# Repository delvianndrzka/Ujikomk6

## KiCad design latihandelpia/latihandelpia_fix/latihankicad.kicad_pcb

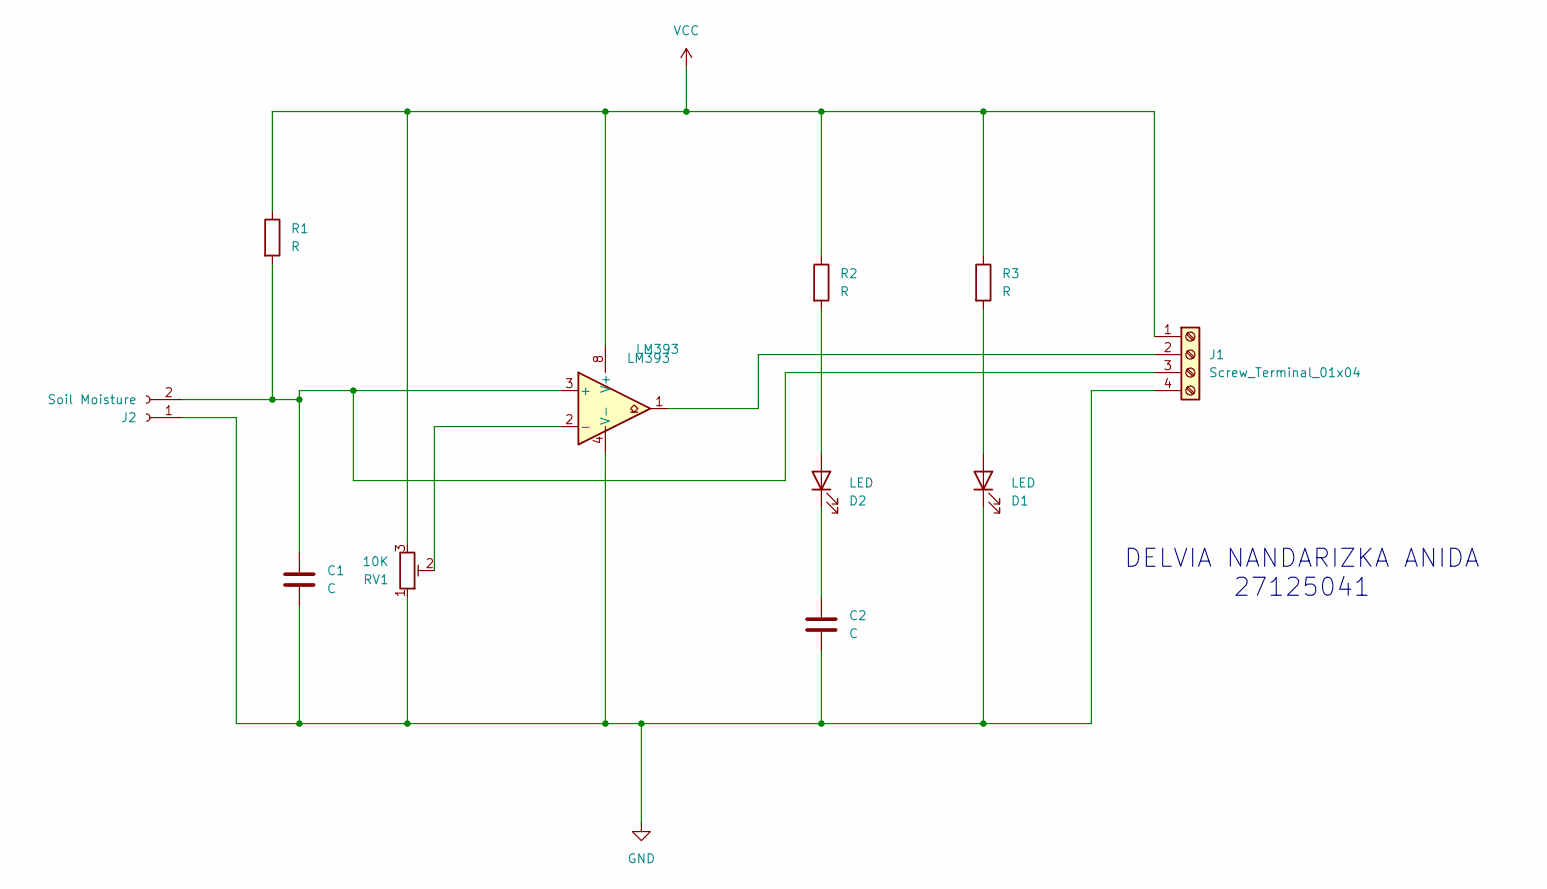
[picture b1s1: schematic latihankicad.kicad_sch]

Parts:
C1, C2: C; C_Axial_L22.0mm_D10.5mm_P27.50mm_Horizontal
D1, D2: LED; LED_D3.0mm_Clear
J1: Screw_Terminal_01x04; TerminalBlock_Phoenix_MPT-0,5-4-2.54_1x04_P2.54mm_Horizontal
J2: Soil Moisture; PinHeader_1x02_P2.00mm_Horizontal
R1, R2, R3: R; R_Axial_Power_L20.0mm_W6.4mm_P25.40mm
RV1: 10K; Potentiometer_Bourns_3339P_Vertical_HandSoldering
U1: LM393; DIP-8_W7.62mm_Socket

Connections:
GND: C1.2, C2.2, D1.1 (K), J1.4, J2.1, RV1.1, U1.4 (V-)
unnamed: D1.2 (A), R3.2
unnamed: D2.2 (A), R2.2
unnamed: C2.1, D2.1 (K)
unnamed: J1.2, U1.1
unnamed: C1.1, J1.3, J2.2, R1.2, U1.3 (+)
unnamed: RV1.2, U1.2 (-)
VCC: J1.1, R1.1, R2.1, R3.1, RV1.3, U1.8 (V+)

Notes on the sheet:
DELVIA NANDARIZKA ANIDA 27125041

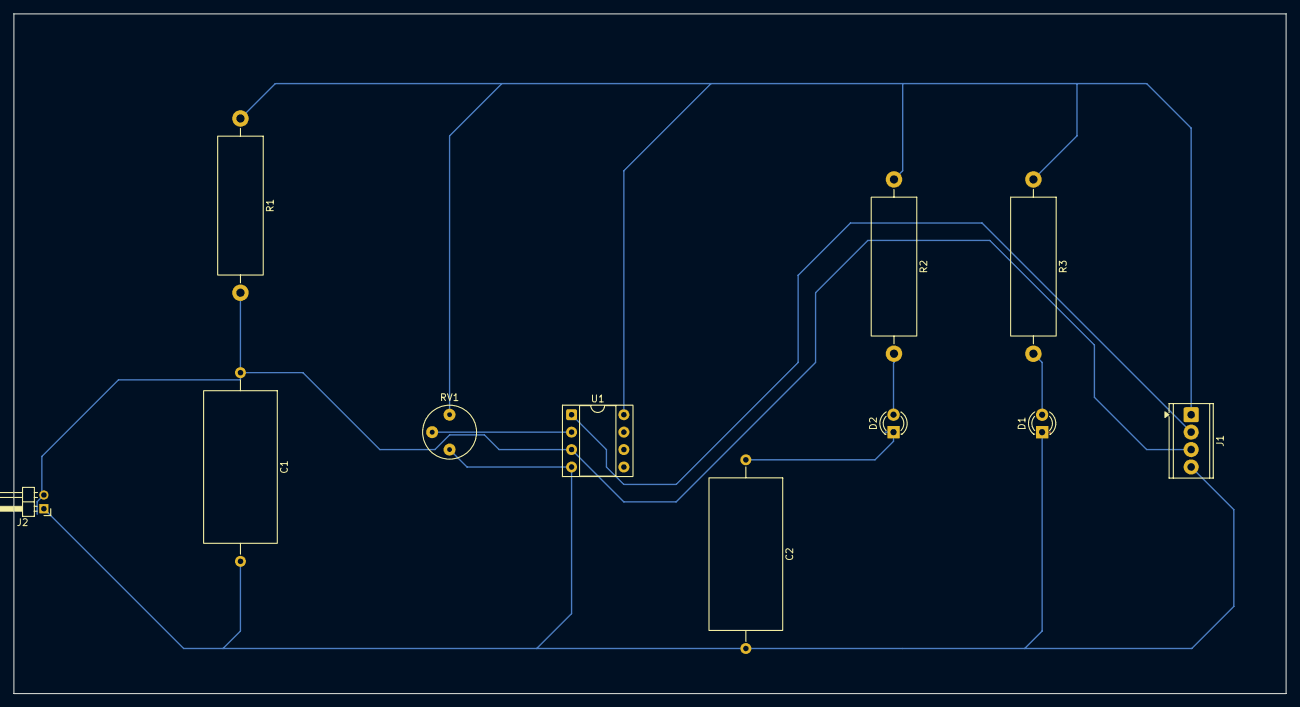
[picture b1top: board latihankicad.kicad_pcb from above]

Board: 2 copper layers, 185.4 x 99.1 mm, 11 parts (0 on the bottom side), 8 nets.
